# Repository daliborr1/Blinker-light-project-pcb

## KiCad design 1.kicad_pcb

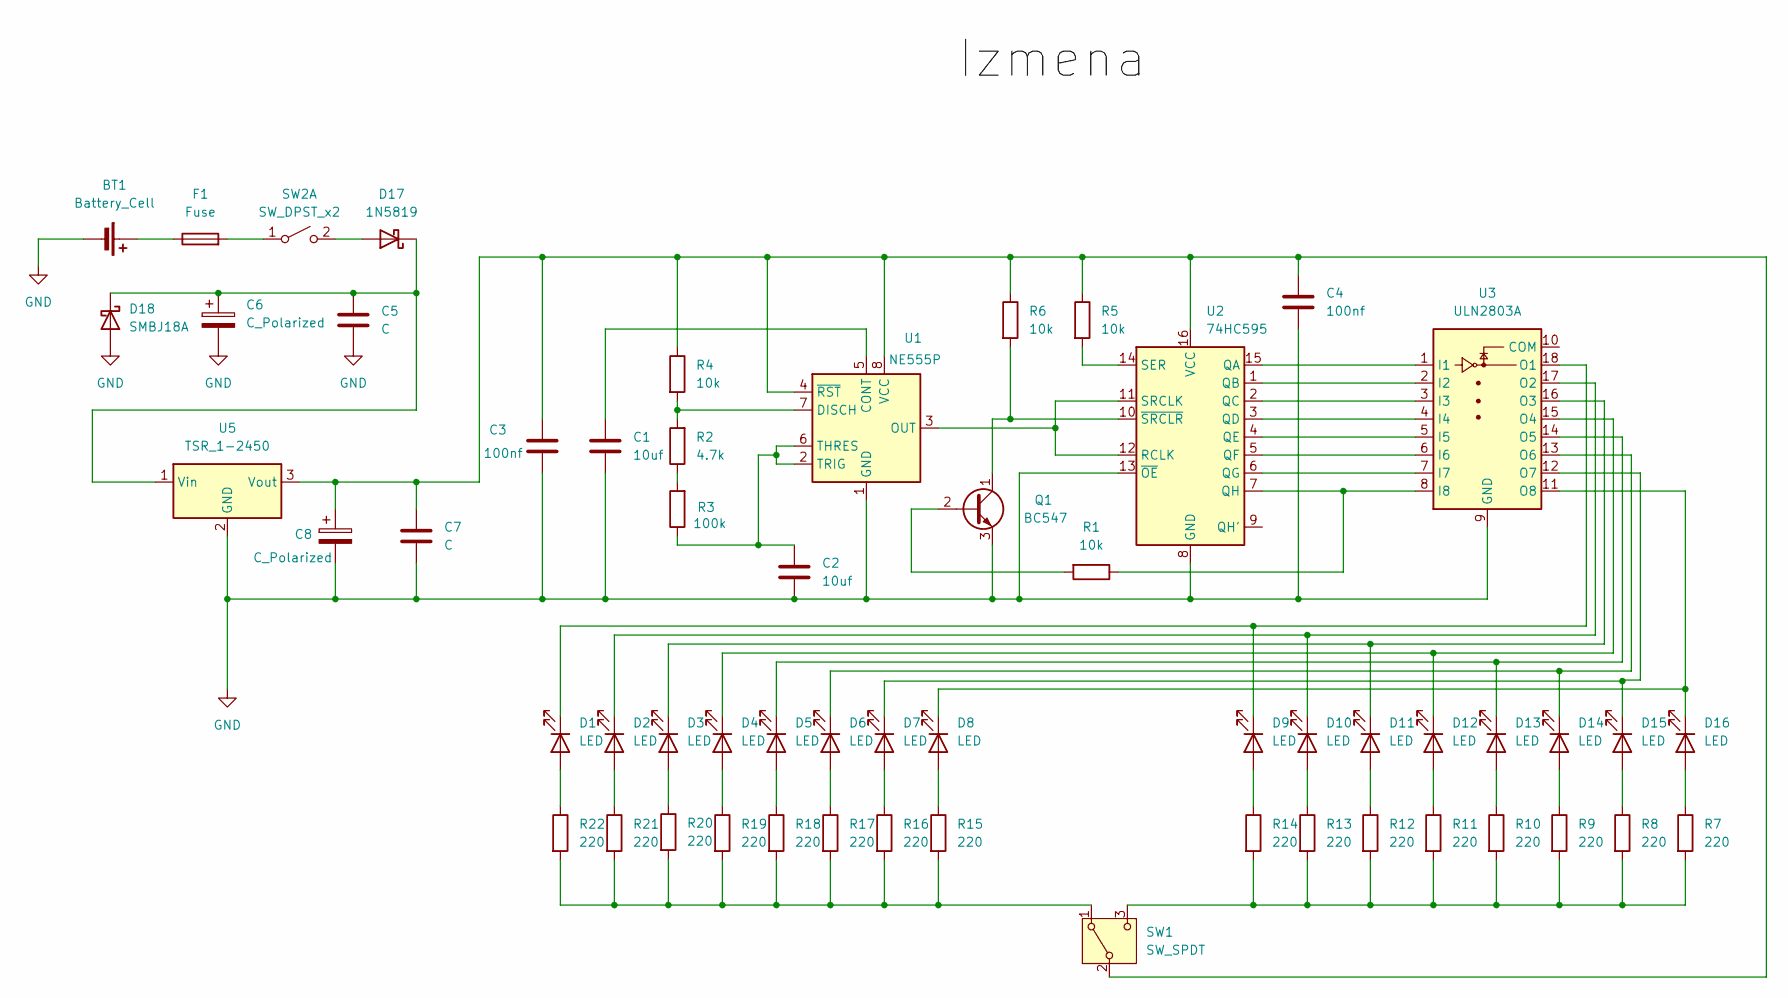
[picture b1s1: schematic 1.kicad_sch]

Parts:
BT1: Battery_Cell; TerminalBlock_MaiXu_MX126-5.0-02P_1x02_P5.00mm
C1, C2: 10uf; CP_Radial_D5.0mm_P2.50mm
C3, C4: 100nf; CP_Radial_D5.0mm_P2.50mm
C5: C; CP_Radial_D5.0mm_P2.50mm
C6, C8: C_Polarized; CP_Radial_Tantal_D5.5mm_P2.50mm
C7: C; CP_Radial_Tantal_D5.5mm_P2.50mm
D1, D2, D3, D4, D5, D6, D7, D8, D9, D10, D11, D12, D13, D14, D15, D16: LED; LED_D5.0mm
D17: 1N5819; D_SMB
D18: SMBJ18A; D_DO-35_SOD27_P10.16mm_Horizontal
F1: Fuse; Fuseholder_Clip-5x20mm_Keystone_3512P_Inline_P23.62x7.27mm_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
Q1: BC547; TO-92_Inline
R1, R4, R5, R6: 10k; R_Axial_DIN0207_L6.3mm_D2.5mm_P7.62mm_Horizontal
R2: 4.7k; R_Axial_DIN0207_L6.3mm_D2.5mm_P7.62mm_Horizontal
R3: 100k; R_Axial_DIN0207_L6.3mm_D2.5mm_P7.62mm_Horizontal
R7, R8, R9, R10, R11, R12, R13, R14, R15, R16, R17, R18, R19, R20, R21, R22: 220; R_Axial_DIN0207_L6.3mm_D2.5mm_P7.62mm_Horizontal
SW1: SW_SPDT; PinHeader_1x03_P2.54mm_Vertical
SW2: SW_DPST_x2; PinHeader_1x02_P2.54mm_Vertical
U1: NE555P; DIP-8_W7.62mm
U2: 74HC595; DIP-16_W7.62mm
U3: ULN2803A; DIP-18_W7.62mm
U5: TSR_1-2450; Converter_DCDC_TRACO_TSR-1_THT

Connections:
GND: BT1.2 (-), C1.1, C2.2, C3.2, C4.2, C5.2, C6.2, C7.2, C8.2, D18.2 (A), Q1.3 (E), U1.1 (GND), U2.8 (GND), U2.13 (~OE), U3.9 (GND), U5.2 (GND); also elsewhere on the board
unnamed 1: BT1.1 (+), F1.1; also elsewhere on the board
unnamed: D1.2 (A), R22.1
unnamed: D1.1 (K), D9.1 (K), U3.18 (O1)
unnamed: D2.2 (A), R21.1
unnamed: D3.2 (A), R20.1
unnamed: D4.2 (A), R19.1
unnamed: D5.2 (A), R18.1
unnamed: D6.2 (A), R17.1
unnamed: D7.2 (A), R16.1
unnamed: D8.2 (A), R15.1
unnamed: D9.2 (A), R14.1
unnamed: D10.2 (A), R13.1
unnamed: D2.1 (K), D10.1 (K), U3.17 (O2)
unnamed: D11.2 (A), R12.1
unnamed: D3.1 (K), D11.1 (K), U3.16 (O3)
unnamed: D12.2 (A), R11.1
unnamed: D4.1 (K), D12.1 (K), U3.15 (O4)
unnamed: D13.2 (A), R10.1
unnamed: D5.1 (K), D13.1 (K), U3.14 (O5)
unnamed: D14.2 (A), R9.1
unnamed: D6.1 (K), D14.1 (K), U3.13 (O6)
unnamed: D15.2 (A), R8.1
unnamed: D7.1 (K), D15.1 (K), U3.12 (O7)
unnamed: D16.2 (A), R7.1
unnamed: D8.1 (K), D16.1 (K), U3.11 (O8)
unnamed: D17.2 (A), SW2.2 (B)
unnamed: C5.1, C6.1, D17.1 (K), D18.1 (K), U5.1 (Vin)
unnamed: Q1.2 (B), R1.2
unnamed: Q1.1 (C), R6.2, U2.10 (~SRCLR)
unnamed: R2.1, R3.2
unnamed: R15.2, R16.2, R17.2, R18.2, R19.2, R20.2, R21.2, R22.2, SW1.1 (A)
unnamed: C3.1, C4.1, C7.1, C8.1, R4.1, R5.1, R6.1, SW1.2 (B), U1.4 (~RST), U1.8 (VCC), U2.16 (VCC), U5.3 (Vout)
unnamed: R7.2, R8.2, R9.2, R10.2, R11.2, R12.2, R13.2, R14.2, SW1.3 (C)
unnamed: F1.2, SW2.1 (A)
unnamed: C1.2, U1.5 (CONT)
unnamed: R2.2, R4.2, U1.7 (DISCH)
unnamed: U1.3 (OUT), U2.11 (SRCLK), U2.12 (RCLK)
unnamed: C2.1, R3.1, U1.2 (TRIG), U1.6 (THRES)
unnamed: U2.15 (QA), U3.1 (I1)
unnamed: U2.1 (QB), U3.2 (I2)
unnamed: U2.2 (QC), U3.3 (I3)
unnamed: U2.3 (QD), U3.4 (I4)
unnamed: U2.4 (QE), U3.5 (I5)
unnamed: U2.5 (QF), U3.6 (I6)
unnamed: U2.6 (QG), U3.7 (I7)
unnamed: R1.1, U2.7 (QH), U3.8 (I8)
unnamed: R5.2, U2.14 (SER)

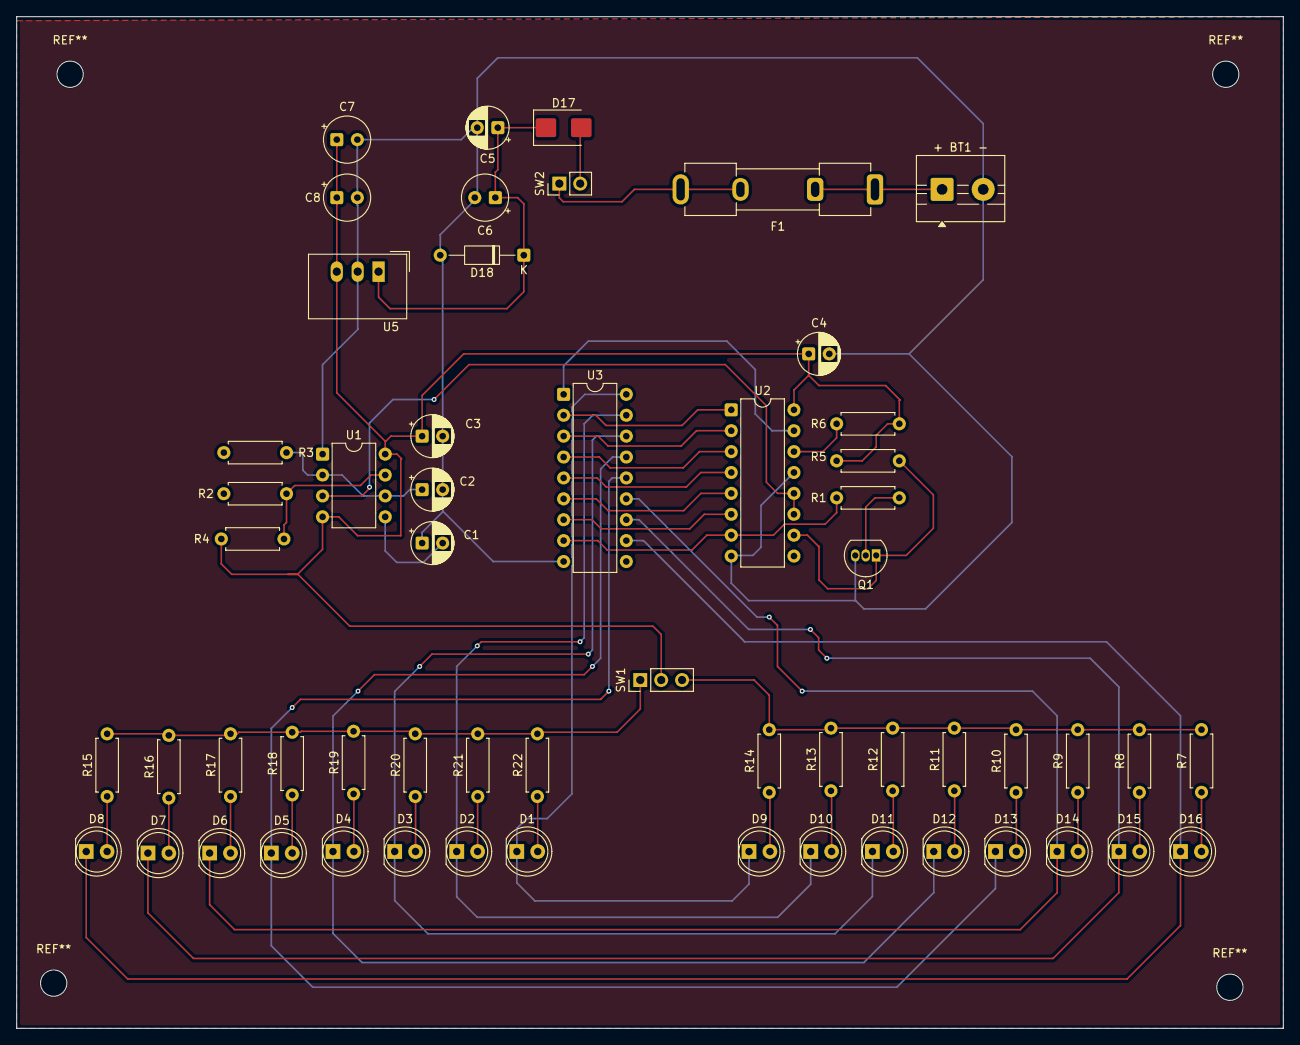
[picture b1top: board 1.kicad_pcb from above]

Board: 2 copper layers, 154.0 x 123.0 mm, 57 parts (0 on the bottom side), 48 nets.

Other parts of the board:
+ BT1 -: + Battery_Cell -; TerminalBlock_MaiXu_MX126-5.0-02P_1x02_P5.00mm

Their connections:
GND: + BT1 -.2 (-); also elsewhere on the board
unnamed 1: + BT1 -.1 (+); also elsewhere on the board
